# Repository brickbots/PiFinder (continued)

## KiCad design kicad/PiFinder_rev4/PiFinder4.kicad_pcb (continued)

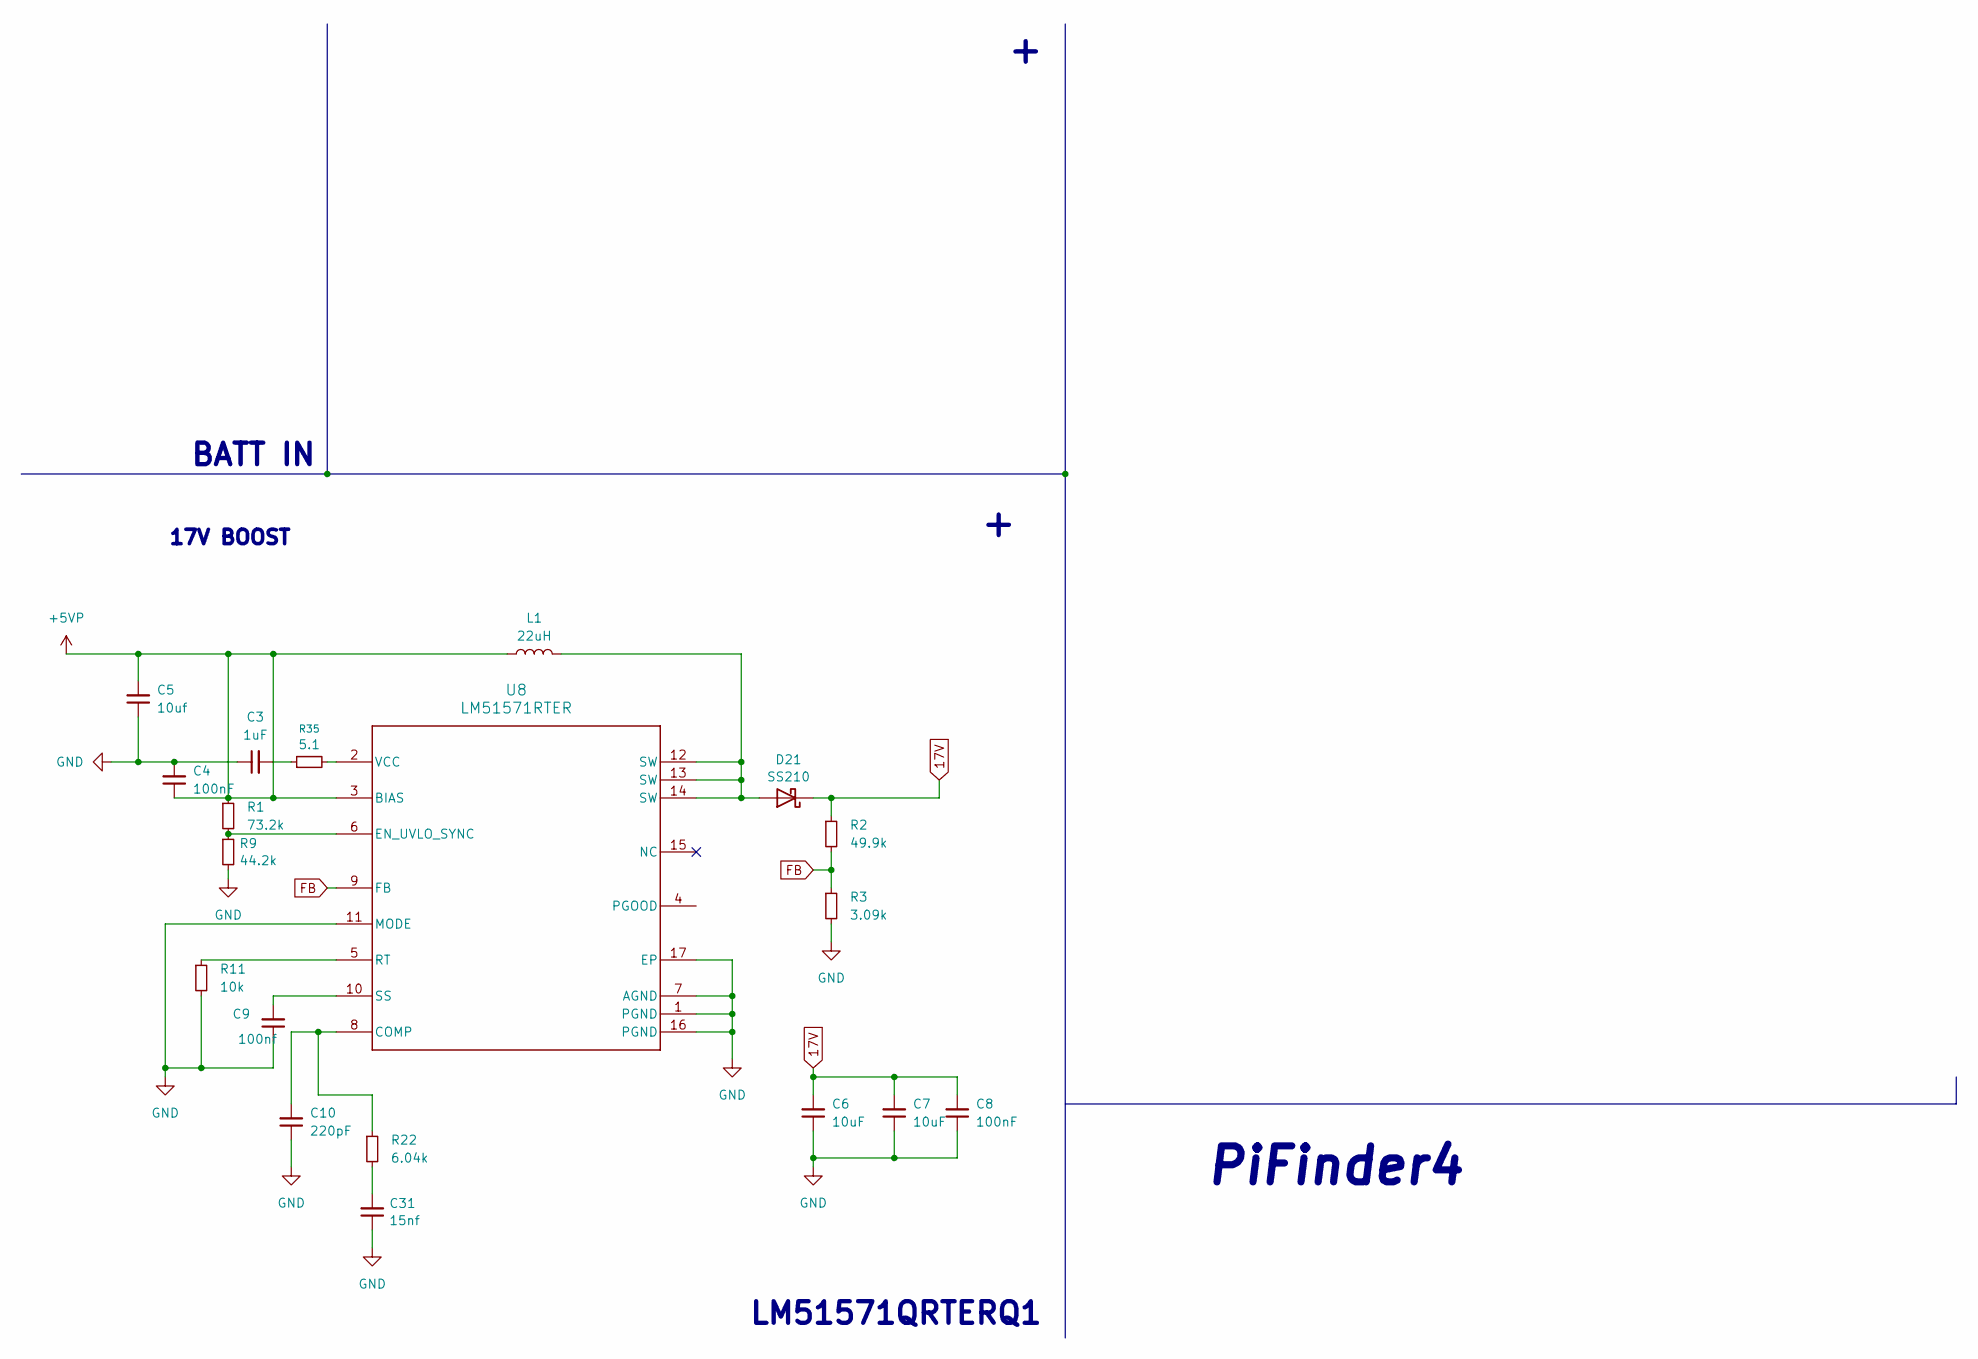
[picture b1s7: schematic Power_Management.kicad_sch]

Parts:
C3: 1uF; C_0603_1608Metric; LCSC C15849
C4, C8: 100nF; C_0603_1608Metric; LCSC C14663
C5: 10uf; C_0805_2012Metric; LCSC C15850
C6, C7: 10uF; C_1206_3216Metric; LCSC C13585
C9: 100nf; C_0603_1608Metric; LCSC C14663
C10: 220pF; C_0402_1005Metric; LCSC C1530
C31: 15nf; C_0402_1005Metric; LCSC C114405
D21: SS210; D_SMA; PARTREV 2; LCSC C14996
L1: 22uH; L_Wurth_WE-LQSH-3012; LCSC C41405943
R1: 73.2k; R_0402_1005Metric; LCSC C26986
R2: 49.9k; R_0402_1005Metric; LCSC C2906873
R3: 3.09k; R_0402_1005Metric; LCSC C11460
R9: 44.2k; R_0402_1005Metric; LCSC C25895
R11: 10k; R_0402_1005Metric; LCSC C25744
R22: 6.04k; R_0402_1005Metric; LCSC C97819
R35: 5.1; R_0402_1005Metric; LCSC C412902
U8: LM51571RTER; LM51571; LCSC C3188430

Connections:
17V: C6.2, C7.2, C8.2, D21.1 (K), R2.1; also elsewhere on the board
+5VP: C4.1, C5.2, L1.1, R1.1, U8.3 (BIAS); also elsewhere on the board
FB: R2.2, R3.1, U8.9 (FB)
GND: C3.1, C4.2, C5.1, C6.1, C7.1, C8.1, C9.1, C10.1, C31.1, R3.2, R9.2, R11.2, U8.1 (PGND), U8.7 (AGND), U8.11 (MODE), U8.16 (PGND), U8.17 (EP); also elsewhere on the board
unnamed: C3.2, R35.1
unnamed: C31.2, R22.2
unnamed: D21.2 (A), L1.2, U8.12 (SW), U8.13 (SW), U8.14 (SW)
unnamed: C10.2, R22.1, U8.8 (COMP)
unnamed: R1.2, R9.1, U8.6 (EN_UVLO_SYNC)
unnamed: R11.1, U8.5 (RT)
unnamed: C9.2, U8.10 (SS)
unnamed: R35.2, U8.2 (VCC)

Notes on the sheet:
17V BOOST
BATT IN
LM51571QRTERQ1
PiFinder4

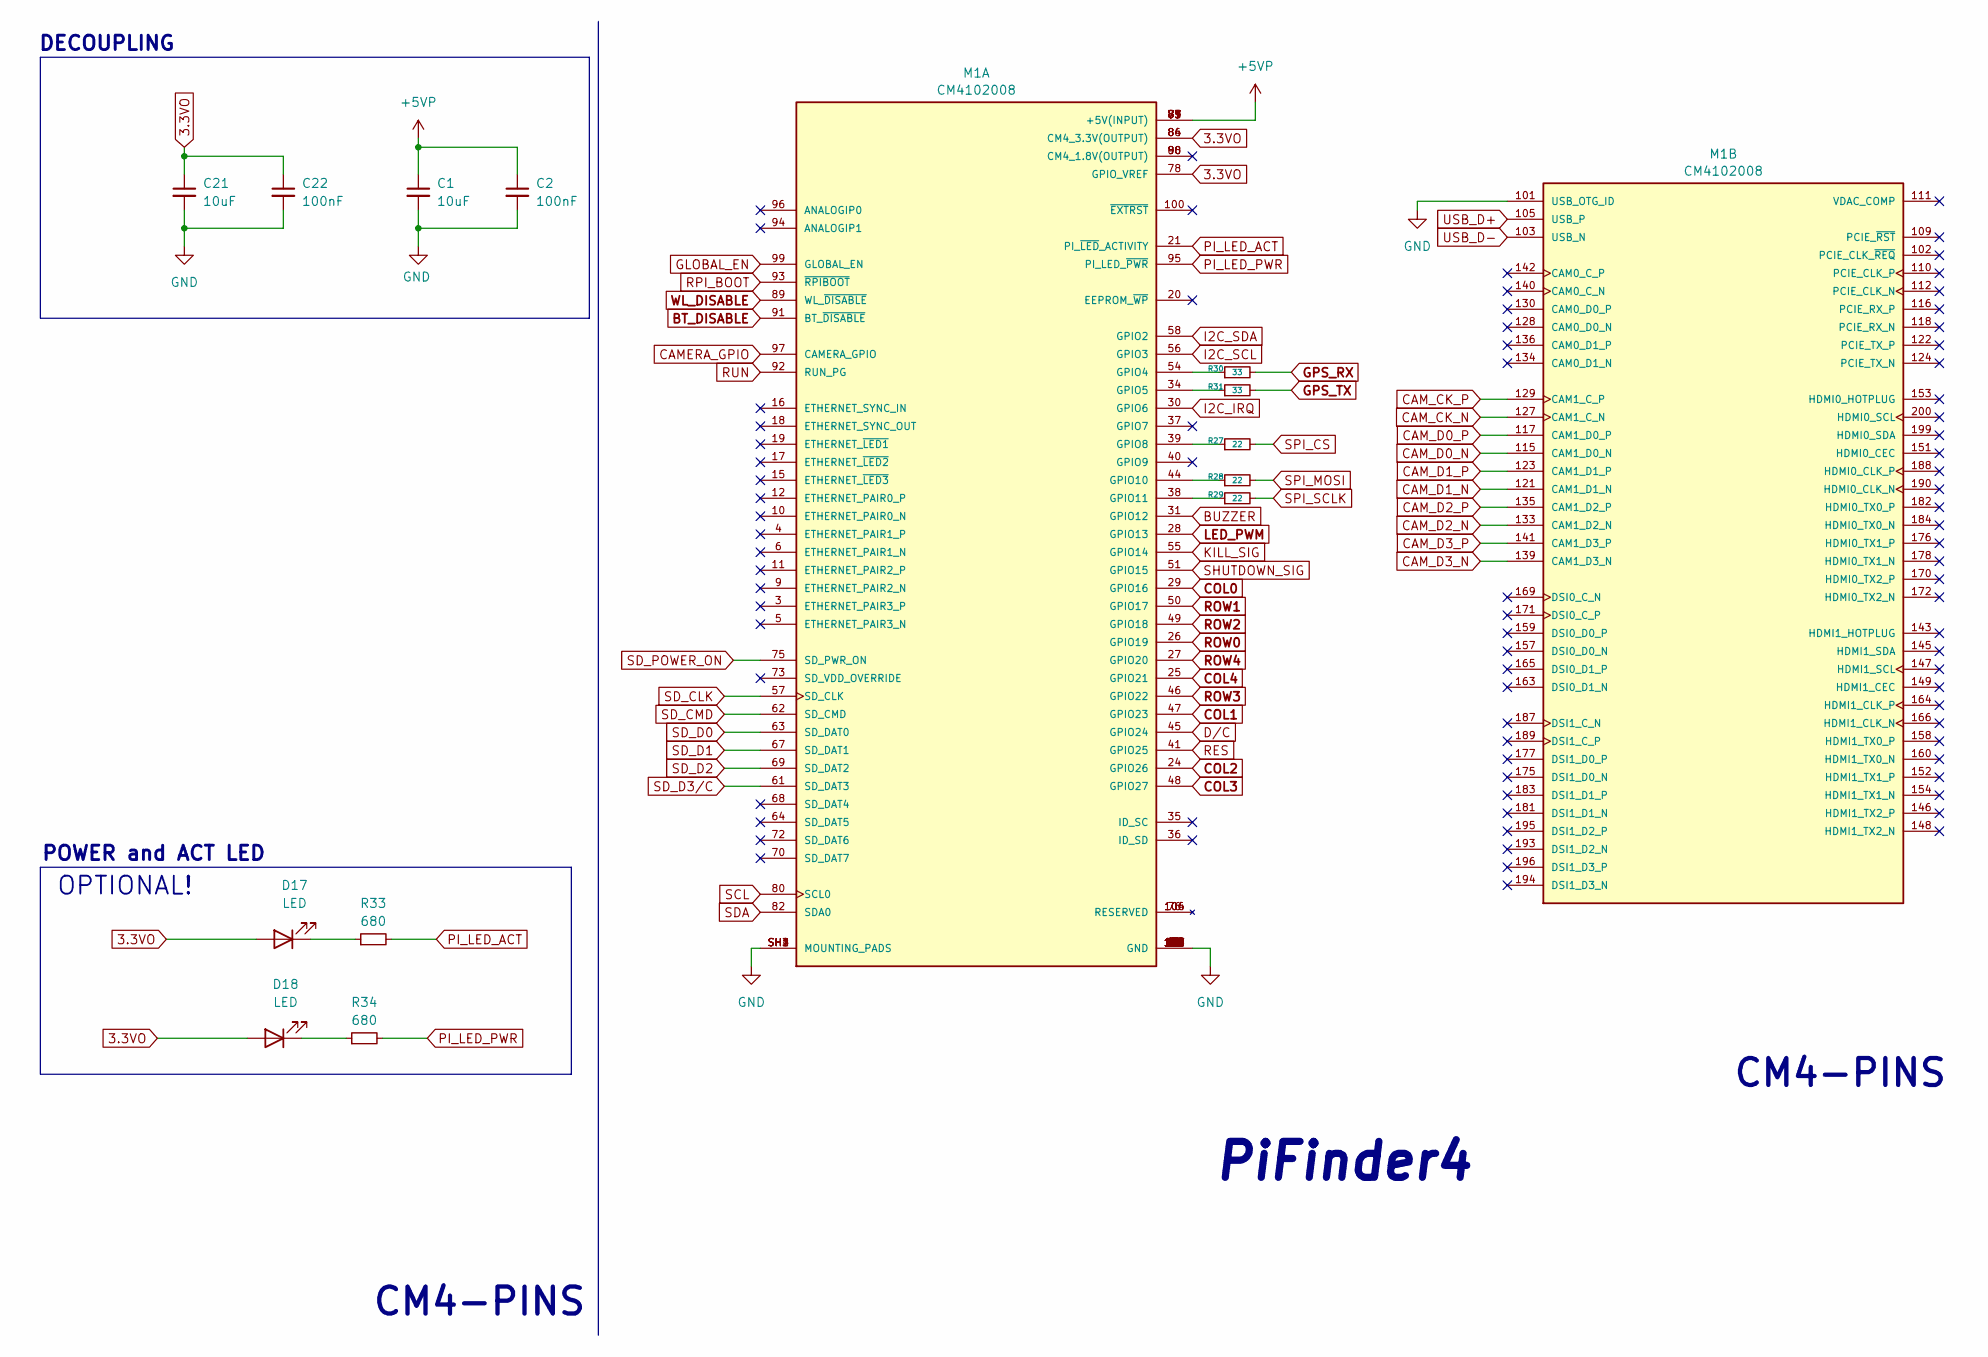
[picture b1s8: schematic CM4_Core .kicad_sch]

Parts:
C1: 10uF; C_0805_2012Metric; LCSC C15850
C2, C22: 100nF; C_0603_1608Metric; LCSC C14663
C21: 10uF; C_0603_1608Metric; LCSC C96446
D17, D18: LED; LED_1210_3225Metric; LCSC C264578
M1: CM4102008; MODULE_CM4102008; PARTREV 2021-10-12; LCSC C597931
R27, R28, R29: 22; R_0402_1005Metric; LCSC C25092
R30, R31: 33; R_0402_1005Metric; LCSC C25105
R33, R34: 680; R_0402_1005Metric; LCSC C137948

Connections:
3.3VO: C21.1, C22.1, D17.2 (A), D18.2 (A), M1.78 (GPIO_VREF), M1.84 (CM4_3.3V(OUTPUT)), M1.86 (CM4_3.3V(OUTPUT)); also elsewhere on the board
+5VP: C1.1, C2.1, M1.77 (+5V(INPUT)), M1.79 (+5V(INPUT)), M1.81 (+5V(INPUT)), M1.83 (+5V(INPUT)), M1.85 (+5V(INPUT)), M1.87 (+5V(INPUT)); also elsewhere on the board
BT_DISABLE: M1.91 (BT_~DISABLE)
BUZZER: M1.31 (GPIO12); also elsewhere on the board
CAMERA_GPIO: M1.97 (CAMERA_GPIO); also elsewhere on the board
CAM_CK_N: M1.127 (CAM1_C_N); also elsewhere on the board
CAM_CK_P: M1.129 (CAM1_C_P); also elsewhere on the board
CAM_D0_N: M1.115 (CAM1_D0_N); also elsewhere on the board
CAM_D0_P: M1.117 (CAM1_D0_P); also elsewhere on the board
CAM_D1_N: M1.121 (CAM1_D1_N); also elsewhere on the board
CAM_D1_P: M1.123 (CAM1_D1_P); also elsewhere on the board
CAM_D2_N: M1.133 (CAM1_D2_N); also elsewhere on the board
CAM_D2_P: M1.135 (CAM1_D2_P); also elsewhere on the board
CAM_D3_N: M1.139 (CAM1_D3_N); also elsewhere on the board
CAM_D3_P: M1.141 (CAM1_D3_P); also elsewhere on the board
COL0: M1.29 (GPIO16); also elsewhere on the board
COL1: M1.47 (GPIO23); also elsewhere on the board
COL2: M1.24 (GPIO26); also elsewhere on the board
COL3: M1.48 (GPIO27); also elsewhere on the board
COL4: M1.25 (GPIO21); also elsewhere on the board
D/C: M1.45 (GPIO24); also elsewhere on the board
GLOBAL_EN: M1.99 (GLOBAL_EN)
GND: C1.2, C2.2, C21.2, C22.2, M1.1 (GND), M1.2 (GND), M1.7 (GND), M1.8 (GND), M1.13 (GND), M1.14 (GND), M1.22 (GND), M1.23 (GND), M1.32 (GND), M1.33 (GND), M1.42 (GND), M1.43 (GND), M1.52 (GND), M1.53 (GND), M1.59 (GND), M1.60 (GND), M1.65 (GND), M1.66 (GND), M1.71 (GND), M1.74 (GND), M1.98 (GND), M1.101 (USB_OTG_ID), M1.107 (GND), M1.108 (GND), M1.113 (GND), M1.114 (GND), M1.119 (GND), M1.120 (GND), M1.125 (GND), M1.126 (GND), M1.131 (GND), M1.132 (GND), M1.137 (GND), M1.138 (GND), M1.144 (GND), M1.150 (GND), M1.155 (GND), M1.156 (GND), M1.161 (GND), M1.162 (GND), M1.167 (GND), M1.168 (GND), M1.173 (GND), M1.174 (GND), M1.179 (GND), M1.180 (GND), M1.185 (GND), M1.186 (GND), M1.191 (GND), M1.192 (GND), M1.197 (GND), M1.198 (GND), M1.SH1 (MOUNTING_PADS), M1.SH2 (MOUNTING_PADS), M1.SH3 (MOUNTING_PADS), M1.SH4 (MOUNTING_PADS); also elsewhere on the board
GPS_RX: R30.2; also elsewhere on the board
GPS_TX: R31.2; also elsewhere on the board
I2C_IRQ: M1.30 (GPIO6)
I2C_SCL: M1.56 (GPIO3); also elsewhere on the board
I2C_SDA: M1.58 (GPIO2); also elsewhere on the board
KILL_SIG: M1.55 (GPIO14); also elsewhere on the board
LED_PWM: M1.28 (GPIO13); also elsewhere on the board
unnamed: D17.1 (K), R33.1
unnamed: D18.1 (K), R34.1
unnamed: M1.54 (GPIO4), R30.1
unnamed: M1.34 (GPIO5), R31.1
unnamed: M1.39 (GPIO8), R27.1
unnamed: M1.44 (GPIO10), R28.1
unnamed: M1.38 (GPIO11), R29.1
PI_LED_ACT: M1.21 (PI_~LED_ACTIVITY), R33.2
PI_LED_PWR: M1.95 (PI_LED_~PWR), R34.2
RES: M1.41 (GPIO25); also elsewhere on the board
ROW0: M1.26 (GPIO19); also elsewhere on the board
ROW1: M1.50 (GPIO17); also elsewhere on the board
ROW2: M1.49 (GPIO18); also elsewhere on the board
ROW3: M1.46 (GPIO22); also elsewhere on the board
ROW4: M1.27 (GPIO20); also elsewhere on the board
RPI_BOOT: M1.93 (~RPIBOOT)
RUN: M1.92 (RUN_PG)
SCL: M1.80 (SCL0); also elsewhere on the board
SDA: M1.82 (SDA0); also elsewhere on the board
SD_CLK: M1.57 (SD_CLK); also elsewhere on the board
SD_CMD: M1.62 (SD_CMD); also elsewhere on the board
SD_D0: M1.63 (SD_DAT0); also elsewhere on the board
SD_D1: M1.67 (SD_DAT1); also elsewhere on the board
SD_D2: M1.69 (SD_DAT2); also elsewhere on the board
SD_D3/C: M1.61 (SD_DAT3); also elsewhere on the board
SD_POWER_ON: M1.75 (SD_PWR_ON); also elsewhere on the board
SHUTDOWN_SIG: M1.51 (GPIO15); also elsewhere on the board
SPI_CS: R27.2; also elsewhere on the board
SPI_MOSI: R28.2; also elsewhere on the board
SPI_SCLK: R29.2; also elsewhere on the board
USB_D+: M1.105 (USB_P); also elsewhere on the board
USB_D-: M1.103 (USB_N); also elsewhere on the board
WL_DISABLE: M1.89 (WL_~DISABLE)

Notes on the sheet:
CM4-PINS
DECOUPLING
POWER and ACT LED
OPTIONAL!
PiFinder4

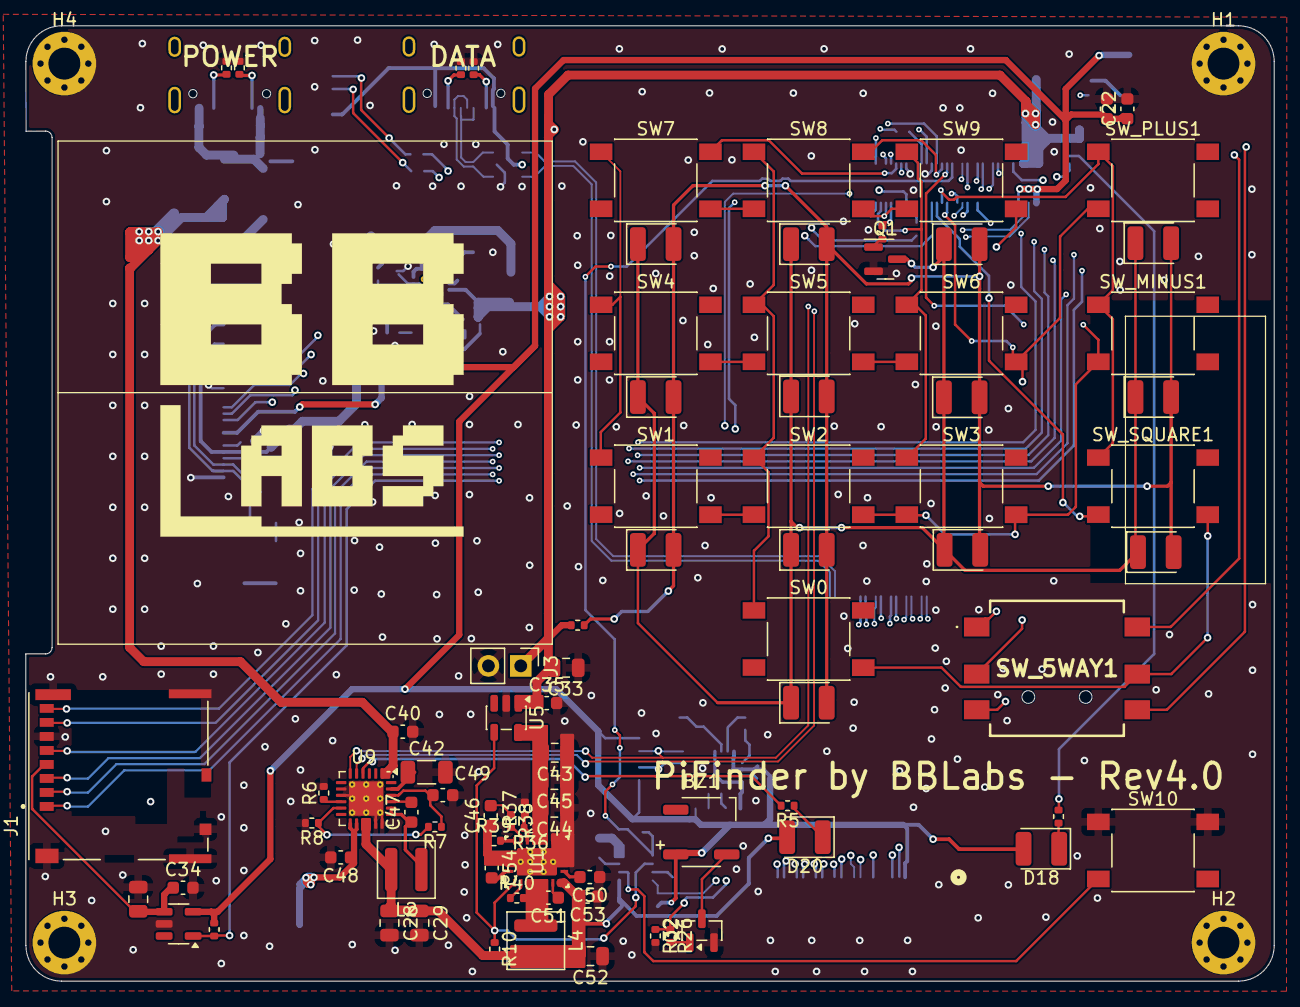
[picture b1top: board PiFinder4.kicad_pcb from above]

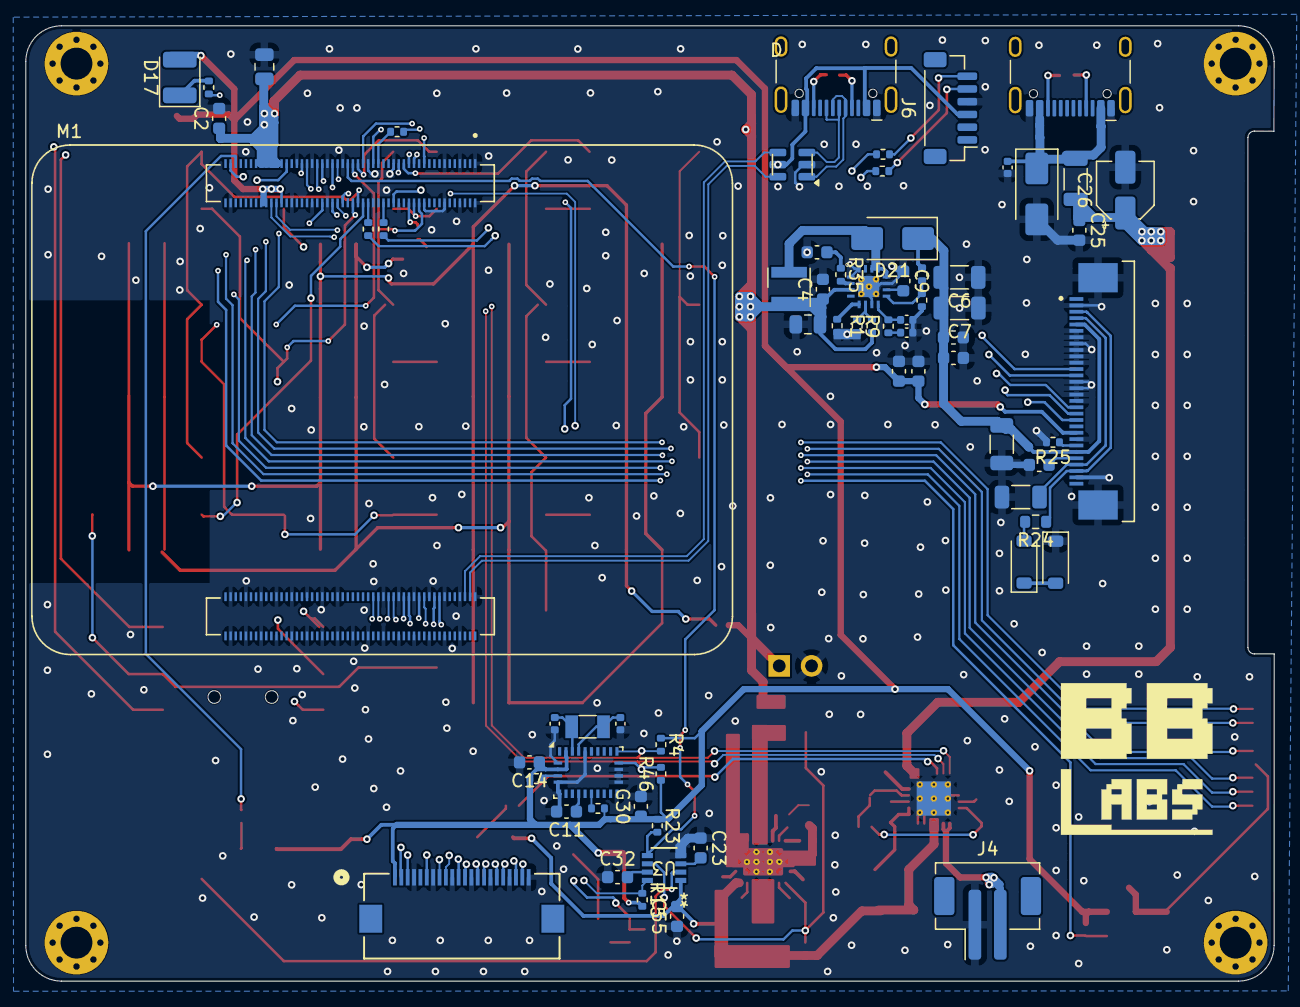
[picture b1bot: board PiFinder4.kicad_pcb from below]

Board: 4 copper layers, 98.0 x 75.0 mm, 155 parts (68 on the bottom side), 116 nets.

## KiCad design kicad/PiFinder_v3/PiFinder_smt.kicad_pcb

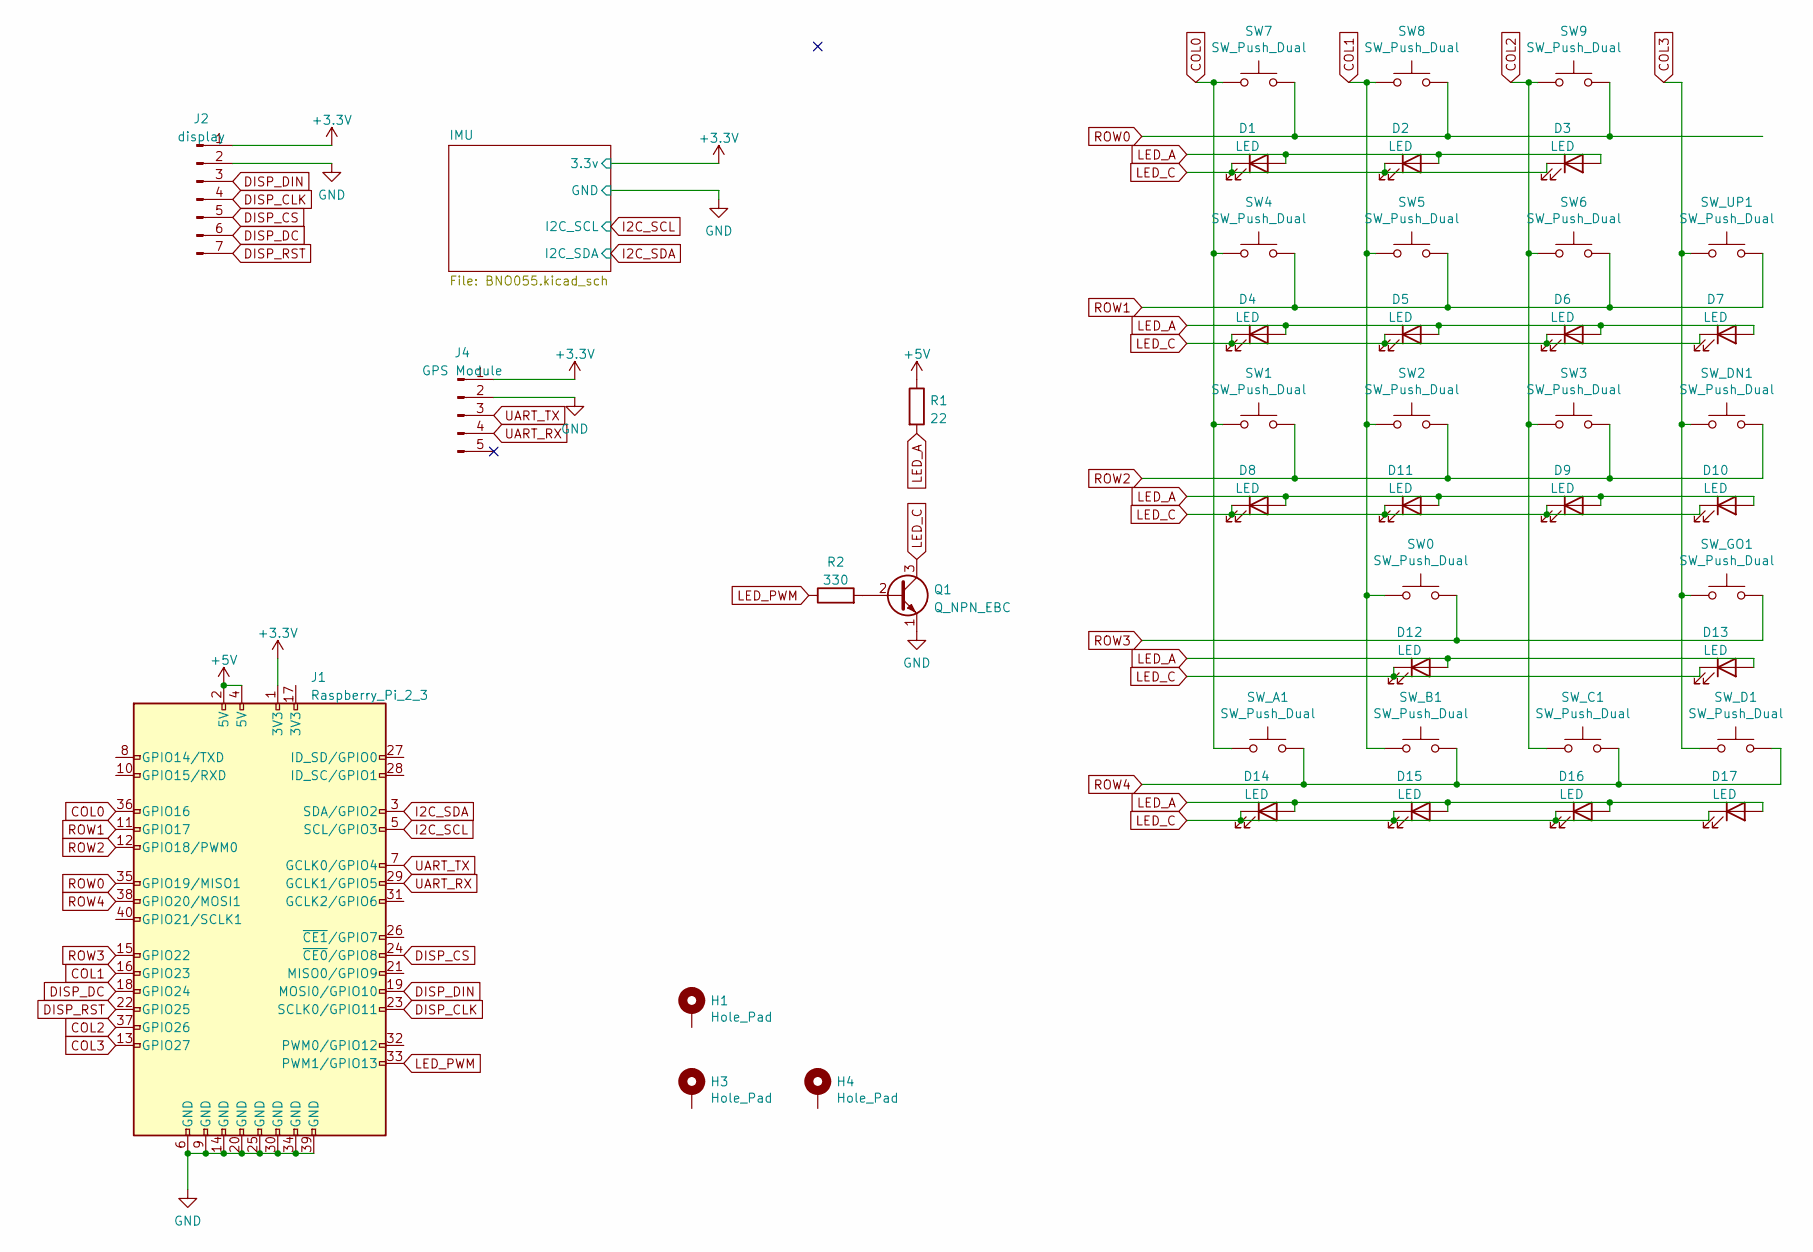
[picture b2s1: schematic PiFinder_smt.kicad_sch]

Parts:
D1, D2, D3, D4, D5, D6, D7, D8, D9, D10, D11, D12, D13, D14, D15, D16, D17: LED; LED_1210_3225Metric; LCSC C125112
H1, H3, H4: Hole_Pad; Mount_M2.5
J1: Raspberry_Pi_2_3; Pin_Header_Straight_2x20
J2: display; Waveshare1.5inOled_flushmount
J4: GPS Module; GT-U7_GPS_smt
Q1: Q_NPN_EBC; PF_SOT-23-NPN; LCSC C280842
R1: 22; R_0805_2012Metric; LCSC C17561
R2: 330; R_0805_2012Metric; LCSC C17630
SW0, SW1, SW2, SW3, SW4, SW5, SW6, SW7, SW8, SW9: SW_Push_Dual; SW_Push_6x6mm_SMT_withhole_tight; LCSC C4364377
SW_A1: SW_Push_Dual; SW_Push_6x6mm_SMT_withhole_tight; LCSC C4364377
SW_B1: SW_Push_Dual; SW_Push_6x6mm_SMT_withhole_tight; LCSC C4364377
SW_C1: SW_Push_Dual; SW_Push_6x6mm_SMT_withhole_tight; LCSC C4364377
SW_D1: SW_Push_Dual; SW_Push_6x6mm_SMT_withhole_tight; LCSC C4364377
SW_DN1: SW_Push_Dual; SW_Push_6x6mm_SMT_withhole_tight; LCSC C4364377
SW_GO1: SW_Push_Dual; SW_Push_6x6mm_SMT_withhole_tight; LCSC C4364377
SW_UP1: SW_Push_Dual; SW_Push_6x6mm_SMT_withhole_tight; LCSC C4364377

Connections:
+3.3V: J1.1 (3V3), J2.1, J4.1; also elsewhere on the board
+5V: J1.2 (5V), J1.4 (5V), R1.1
COL0: J1.36 (GPIO16), SW1.1, SW4.1, SW7.1, SW_A1.1
COL1: J1.16 (GPIO23), SW0.1, SW2.1, SW5.1, SW8.1, SW_B1.1
COL2: J1.37 (GPIO26), SW3.1, SW6.1, SW9.1, SW_C1.1
COL3: J1.13 (GPIO27), SW_D1.1, SW_DN1.1, SW_GO1.1, SW_UP1.1
DISP_CLK: J1.23 (SCLK0/GPIO11), J2.4
DISP_CS: J1.24 (~CE0/GPIO8), J2.5
DISP_DC: J1.18 (GPIO24), J2.6
DISP_DIN: J1.19 (MOSI0/GPIO10), J2.3
DISP_RST: J1.22 (GPIO25), J2.7
GND: J1.6 (GND), J1.9 (GND), J1.14 (GND), J1.20 (GND), J1.25 (GND), J1.30 (GND), J1.34 (GND), J1.39 (GND), J2.2, J4.2, Q1.1 (E); also elsewhere on the board
I2C_SCL: J1.5 (SCL/GPIO3); also elsewhere on the board
I2C_SDA: J1.3 (SDA/GPIO2); also elsewhere on the board
LED_A: D1.2 (A), D2.2 (A), D3.2 (A), D4.2 (A), D5.2 (A), D6.2 (A), D7.2 (A), D8.2 (A), D9.2 (A), D10.2 (A), D11.2 (A), D12.2 (A), D13.2 (A), D14.2 (A), D15.2 (A), D16.2 (A), D17.2 (A), R1.2
LED_C: D1.1 (K), D2.1 (K), D3.1 (K), D4.1 (K), D5.1 (K), D6.1 (K), D7.1 (K), D8.1 (K), D9.1 (K), D10.1 (K), D11.1 (K), D12.1 (K), D13.1 (K), D14.1 (K), D15.1 (K), D16.1 (K), D17.1 (K), Q1.3 (C)
LED_PWM: J1.33 (PWM1/GPIO13), R2.1
unnamed: Q1.2 (B), R2.2
ROW0: J1.35 (GPIO19/MISO1), SW7.2, SW8.2, SW9.2
ROW1: J1.11 (GPIO17), SW4.2, SW5.2, SW6.2, SW_UP1.2
ROW2: J1.12 (GPIO18/PWM0), SW1.2, SW2.2, SW3.2, SW_DN1.2
ROW3: J1.15 (GPIO22), SW0.2, SW_GO1.2
ROW4: J1.38 (GPIO20/MOSI1), SW_A1.2, SW_B1.2, SW_C1.2, SW_D1.2
UART_RX: J1.29 (GCLK1/GPIO5), J4.4
UART_TX: J1.7 (GCLK0/GPIO4), J4.3

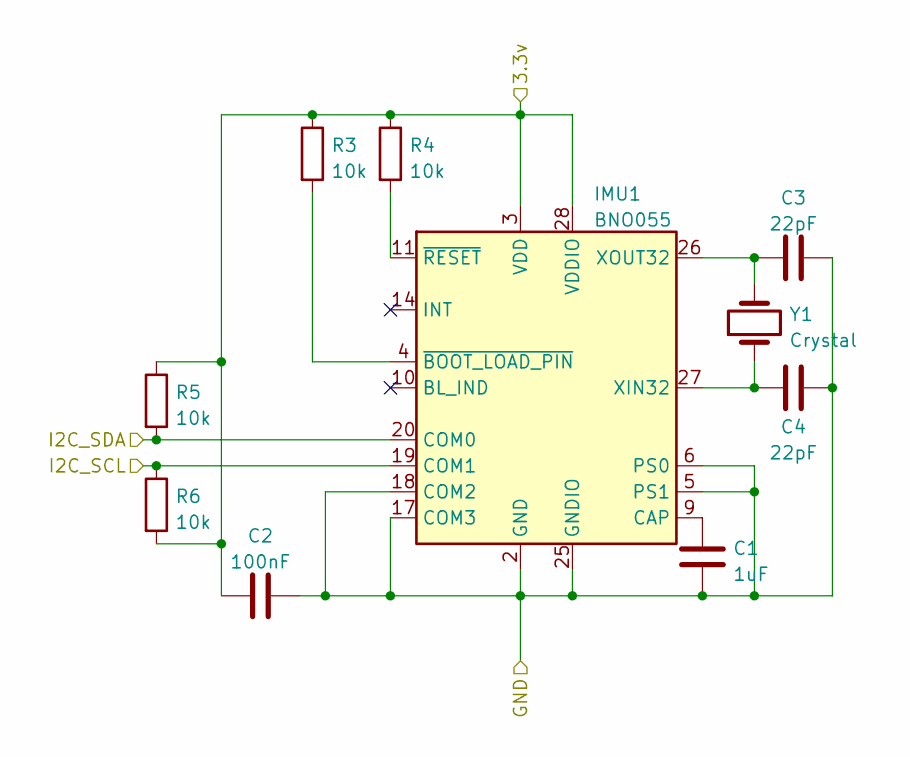
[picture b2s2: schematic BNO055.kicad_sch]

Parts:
C1: 1uF; C_0805_2012Metric; LCSC C2940738
C2: 100nF; C_0805_2012Metric; LCSC C49678
C3, C4: 22pF; C_0805_2012Metric; LCSC C24658
IMU1: BNO055; LGA-28_5.2x3.8mm_P0.5mm; LCSC C93216
R3, R4, R5, R6: 10k; R_0805_2012Metric; LCSC C17414
Y1: Crystal; Crystal_SMD_3215-2Pin_3.2x1.5mm; LCSC C5366532

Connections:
+3.3V: C2.1, IMU1.3 (VDD), IMU1.28 (VDDIO), R3.1, R4.1, R5.1, R6.2; also elsewhere on the board
GND: C1.2, C2.2, C3.2, C4.2, IMU1.2 (GND), IMU1.5 (PS1), IMU1.6 (PS0), IMU1.15 (GNDIO), IMU1.16 (GNDIO), IMU1.17 (COM3), IMU1.18 (COM2), IMU1.25 (GNDIO); also elsewhere on the board
I2C_SCL: IMU1.19 (COM1), R6.1; also elsewhere on the board
I2C_SDA: IMU1.20 (COM0), R5.2; also elsewhere on the board
unnamed: C1.1, IMU1.9 (CAP)
unnamed: C3.1, IMU1.26 (XOUT32), Y1.2
unnamed: C4.1, IMU1.27 (XIN32), Y1.1
unnamed: IMU1.4 (~BOOT_LOAD_PIN), R3.2
unnamed: IMU1.11 (~RESET), R4.2

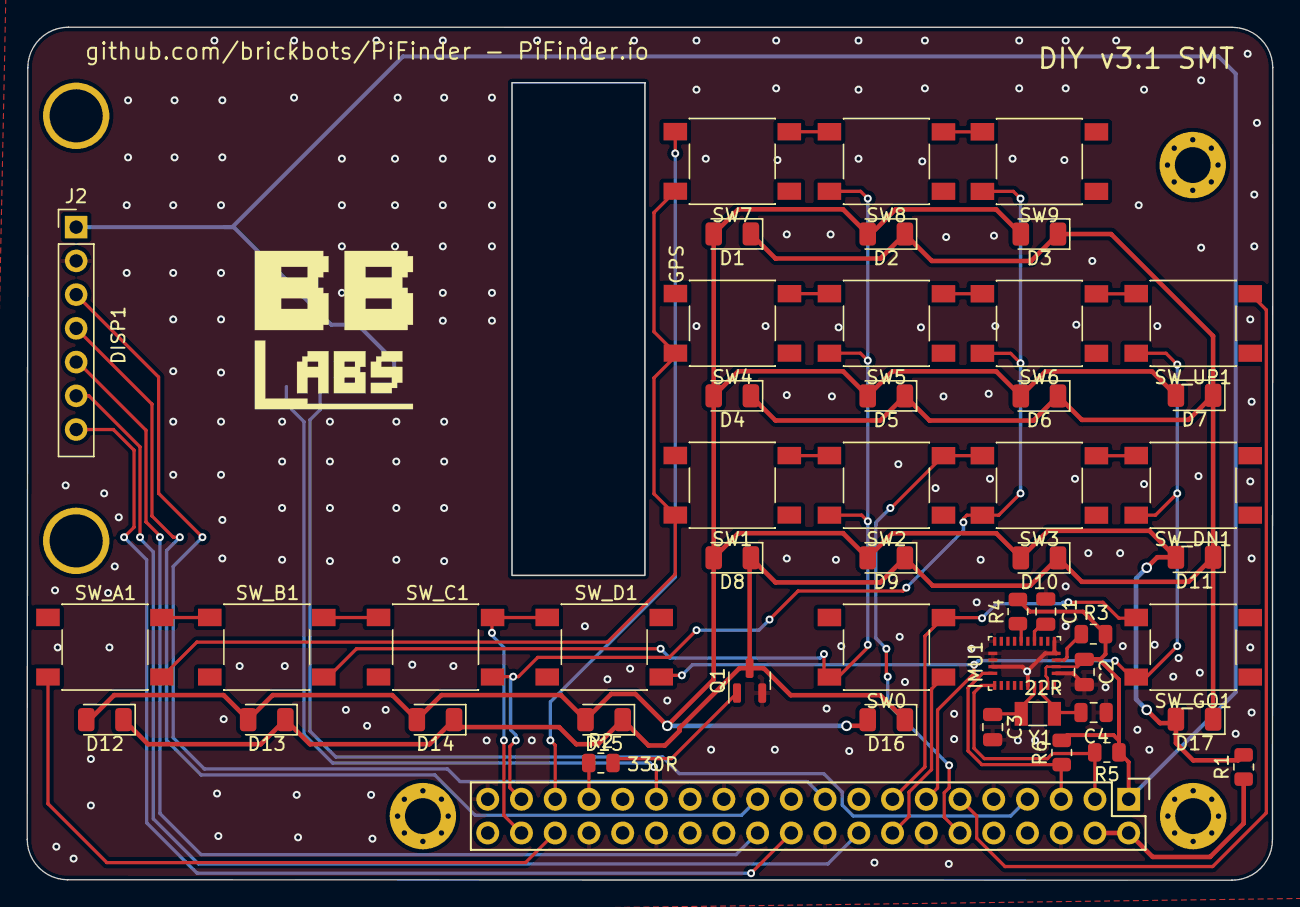
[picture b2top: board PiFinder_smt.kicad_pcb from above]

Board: 2 copper layers, 93.8 x 64.2 mm, 53 parts (1 on the bottom side), 30 nets.

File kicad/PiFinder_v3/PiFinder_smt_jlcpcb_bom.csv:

Comment,Designator,Footprint,LCSC
"1uF","C1","Capacitor_SMD:C_0805_2012Metric","C2940738"
"100nF","C2","Capacitor_SMD:C_0805_2012Metric","C49678"
"22pF","C3,C4","Capacitor_SMD:C_0805_2012Metric","C24658"
"LED","D1,D2,D3,D4,D5,D6,D7,D8,D9,D10,D11,D12,D13,D14,D15,D16,D17","LED_SMD:LED_1210_3225Metric","C125112"
"BNO055","IMU1","Package_LGA:LGA-28_5.2x3.8mm_P0.5mm","C93216"
"Q_NPN_EBC","Q1","RSU:PF_SOT-23-NPN","C280842"
"22","R1","Resistor_SMD:R_0805_2012Metric","C17561"
"330","R2","Resistor_SMD:R_0805_2012Metric","C17630"
"10k","R3,R4,R5,R6","Resistor_SMD:R_0805_2012Metric","C17414"
"SW_Push_Dual","SW0,SW1,SW_A1,SW_B1,SW_C1,SW_D1,SW_DN1,SW_GO1,SW_UP1,SW2,SW3,SW4,SW5,SW6,SW7,SW8,SW9","RSU:SW_Push_6x6mm_SMT_withhole_tight","C4364377"
"Crystal","Y1","Crystal:Crystal_SMD_3215-2Pin_3.2x1.5mm","C5366532"
